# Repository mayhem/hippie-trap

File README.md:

# led-chandelier
LED bottle chandelier built for Nowhere 2015

by Robert Kaye and David Martin

Mock-up
=======

For a render of what we think this might look like a look in the design folder.

Hardware notes
==============

The chandalier made up of about 100 bottles that will have circuit boards with LEDs
inside them. 4 RGD LEDs (WS2812B) connected to an atmega128 will light up each bottle.
Communication happens over a bone simple serial connection, hopefully at 250kbps.
For serial timing and ram reasons, I chose the atmega128 over the attiny84.

The bottles will be connected to 5V power, ground and a communication line. The communication
will be via a line driver that broadcasts the serial signal to each bottle. The RPi can then
send either color information to each bottle or more interestingly send a crude set of instructions
on how to build a color animation. This way the chanelier can work in a centrally coordinated
mode or each bottle carrying out its own program.

.brd and .sch files for Eagle are in hardware folder.

Notes about the circuit
-----------------------

- Regulated 5V power supply in the body of the chandelier
- WS2812B LEDS: http://www.adafruit.com/datasheets/WS2812B.pdf
- MCU: atmega168
- Shottky diodes on the inputs.
- Program via a pogoplug, no actual connector will be on the board.

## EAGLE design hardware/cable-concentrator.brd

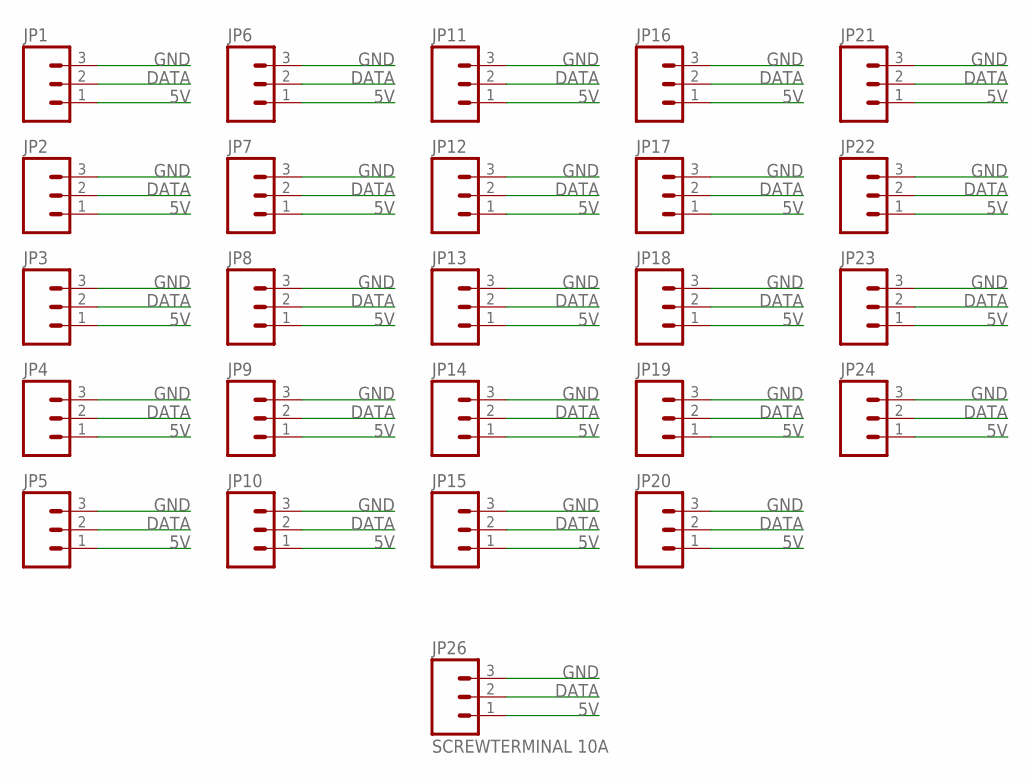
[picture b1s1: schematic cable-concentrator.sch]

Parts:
JP1, JP2, JP3, JP4, JP5, JP6, JP7, JP8, JP9, JP10, JP11, JP12, JP13, JP14, JP15, JP16, JP17, JP18, JP19, JP20, JP21, JP22, JP23, JP24: M03PTH; 1X03
JP26: SCREWTERMINAL 10A; SCREWTERMINAL-3.5MM-3

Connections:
5V: JP1.1, JP2.1, JP3.1, JP4.1, JP5.1, JP6.1, JP7.1, JP8.1, JP9.1, JP10.1, JP11.1, JP12.1, JP13.1, JP14.1, JP15.1, JP16.1, JP17.1, JP18.1, JP19.1, JP20.1, JP21.1, JP22.1, JP23.1, JP24.1, JP26.1
DATA: JP1.2, JP2.2, JP3.2, JP4.2, JP5.2, JP6.2, JP7.2, JP8.2, JP9.2, JP10.2, JP11.2, JP12.2, JP13.2, JP14.2, JP15.2, JP16.2, JP17.2, JP18.2, JP19.2, JP20.2, JP21.2, JP22.2, JP23.2, JP24.2, JP26.2
GND: JP1.3, JP2.3, JP3.3, JP4.3, JP5.3, JP6.3, JP7.3, JP8.3, JP9.3, JP10.3, JP11.3, JP12.3, JP13.3, JP14.3, JP15.3, JP16.3, JP17.3, JP18.3, JP19.3, JP20.3, JP21.3, JP22.3, JP23.3, JP24.3, JP26.3

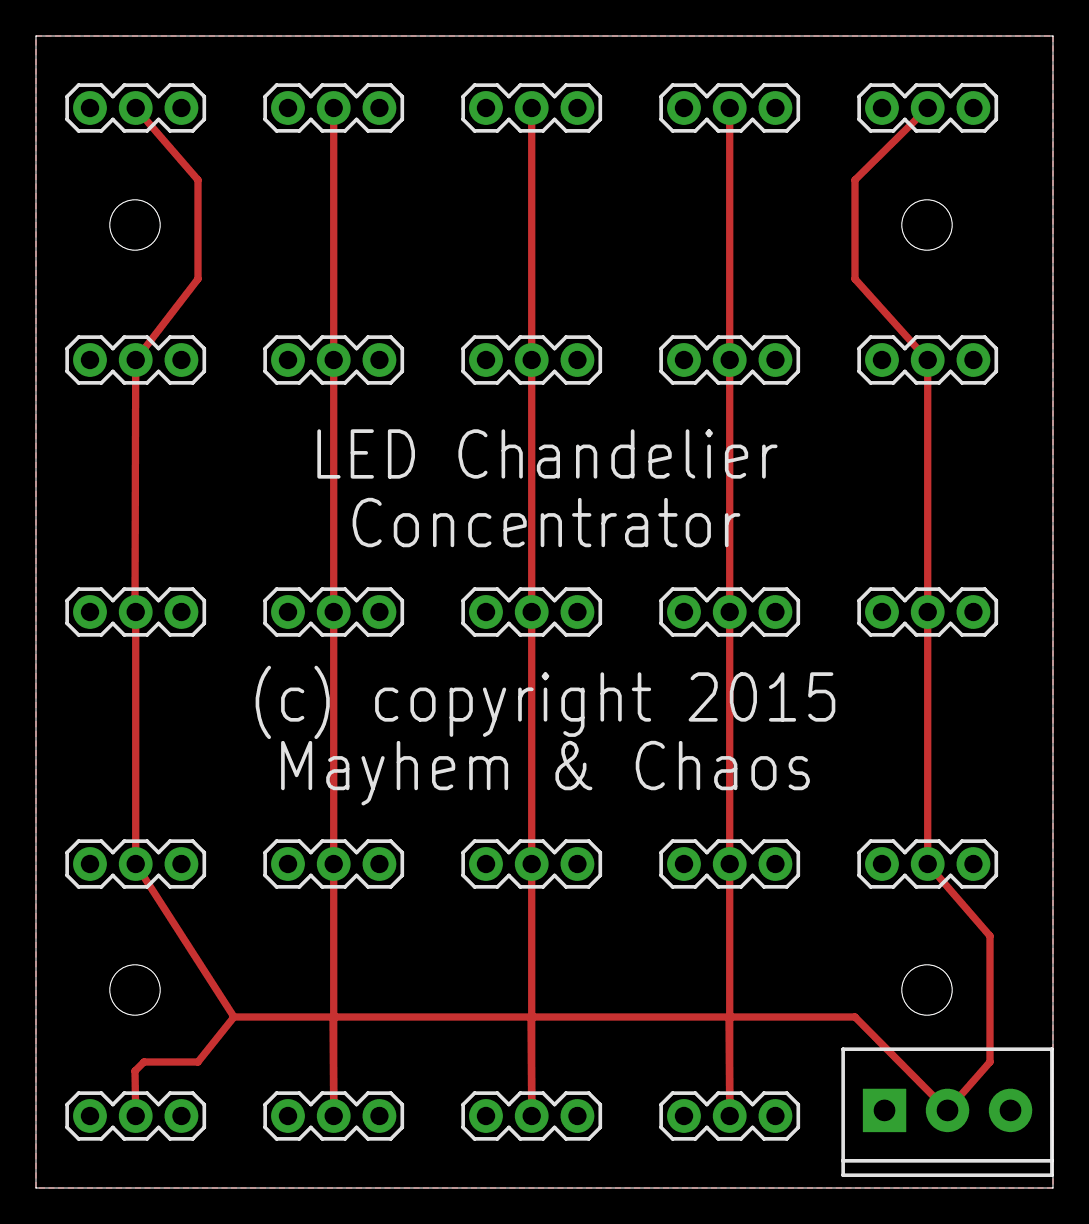
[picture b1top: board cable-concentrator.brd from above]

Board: 2 copper layers, 56.5 x 64.0 mm, 25 parts (0 on the bottom side), 3 nets.

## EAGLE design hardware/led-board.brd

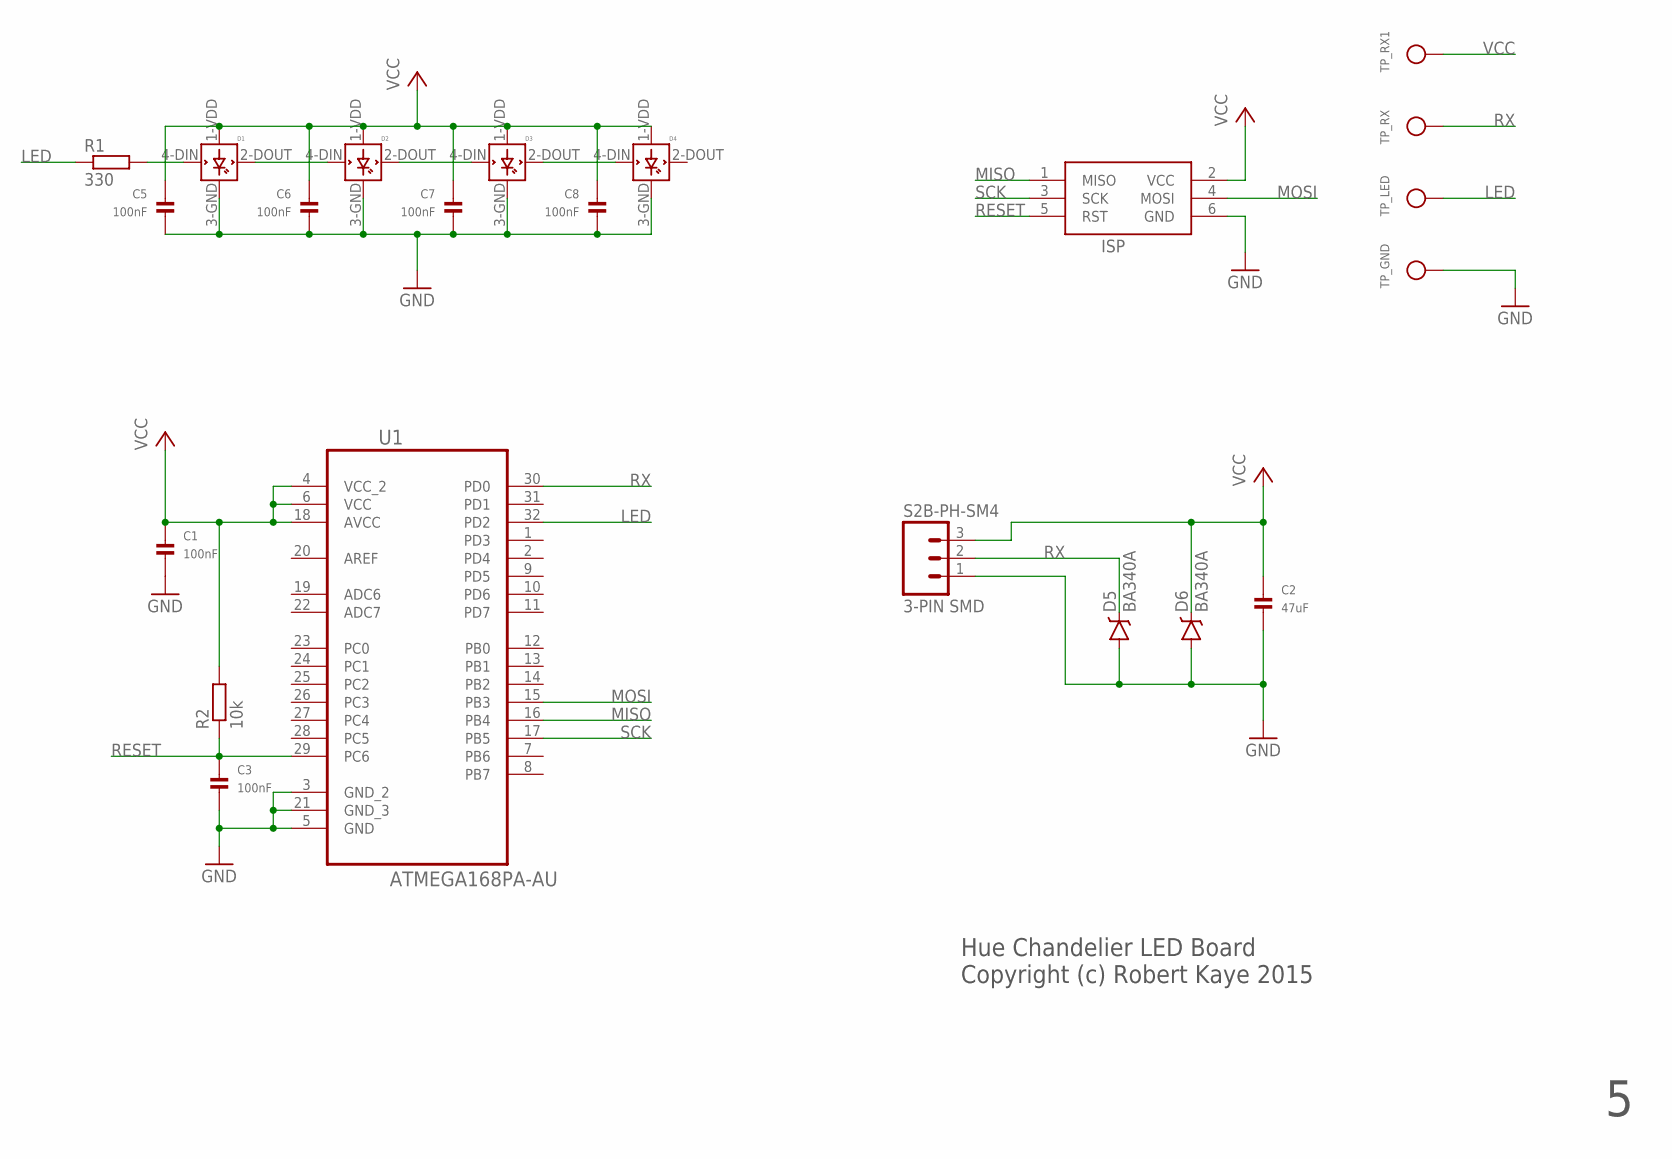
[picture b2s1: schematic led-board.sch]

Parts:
C1, C3, C5, C6, C7, C8: 100nF; 0805; MPN MCSH21B104K250CT
C2: 47uF; 1206; MPN CC0805KKX7R7BB105
D1, D2, D3, D4: WS2812B; MPN WS2812B
D5, D6: BA340A; SMA-DIODE; MPN B330A-13-F
ISP: AVRISP-6; AVRISP
R1: 330; R0805; MPN RC0805JR-07330RL
R2: 10k; R0805; MPN RT0805FRE0710KL
S2B-PH-SM4: 3-PIN SMD; JST-3-SMD; MPN S3B-PH-SM4-TB(LF)(SN)
TP_GND: TESTPOINT1.5X2.0MM_NOCREAM; PAD-1.5X2.0
TP_LED: TESTPOINT1.5X2.0MM_NOCREAM; PAD-1.5X2.0
TP_RX, TP_RX1: TESTPOINT1.5X2.0MM_NOCREAM; PAD-1.5X2.0
U1: ATMEGA168PA-AU; QFP80P900X900X120-32N

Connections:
D3: D2.2-DOUT (DOUT), D3.4-DIN (DIN)
GND: C1.2, C2.2, C3.2, C5.2, C6.2, C7.2, C8.2, D1.3-GND (GND), D2.3-GND (GND), D3.3-GND (GND), D4.3-GND (GND), D5.A, D6.A, ISP.6 (GND), S2B-PH-SM4.1, TP_GND.P$1, U1.3 (GND_2), U1.5 (GND), U1.21 (GND_3)
LED: R1.1, TP_LED.P$1, U1.32 (PD2)
MISO: ISP.1 (MISO), U1.16 (PB4)
MOSI: ISP.4 (MOSI), U1.15 (PB3)
unnamed: D3.2-DOUT (DOUT), D4.4-DIN (DIN)
unnamed: D1.2-DOUT (DOUT), D2.4-DIN (DIN)
unnamed: D1.4-DIN (DIN), R1.2
RESET: C3.1, ISP.5 (RST), R2.1, U1.29 (PC6)
RX: D5.C, S2B-PH-SM4.2, TP_RX.P$1, U1.30 (PD0)
SCK: ISP.3 (SCK), U1.17 (PB5)
VCC: C1.1, C2.1, C5.1, C6.1, C7.1, C8.1, D1.1-VDD (VDD), D2.1-VDD (VDD), D3.1-VDD (VDD), D4.1-VDD (VDD), D6.C, ISP.2 (VCC), R2.2, S2B-PH-SM4.3, TP_RX1.P$1, U1.4 (VCC_2), U1.6 (VCC), U1.18 (AVCC)

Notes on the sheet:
Hue Chandelier LED Board Copyright (c) Robert Kaye 2015

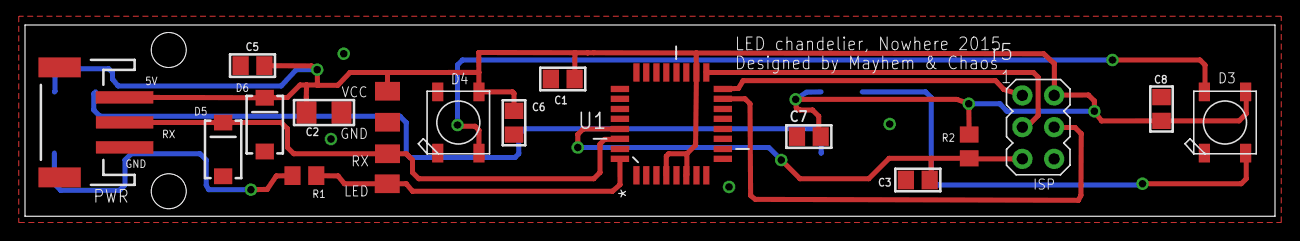
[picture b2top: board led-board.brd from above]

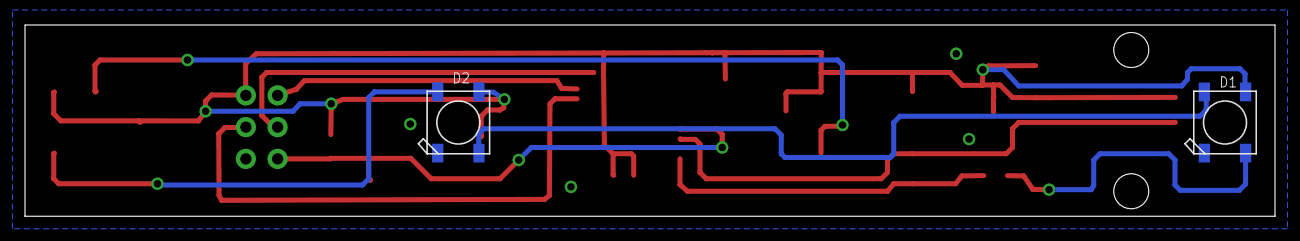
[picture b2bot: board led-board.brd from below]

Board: 2 copper layers, 100.0 x 15.3 mm, 22 parts (2 on the bottom side), 12 nets.

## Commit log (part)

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2015-04-09 Only darkness before this commit
2015-04-09 Added the basic node firmware
2015-04-09 Finished layout and silkscreen work
2015-04-10 test version of a master node
2015-04-10 Brining in the proof of concept RPI code
2015-04-11 Got basic serial comms working
2015-04-11 Basic working node code, updated schematic and layout
2015-04-13 Fixed the orientation of the shottky diodes, improved the layout a bit
2015-04-13 Finished layot and silkscreening. Hopefully ready to go!
2015-04-13 Update README.md
    Adding names.
2015-04-14 Added mounting holes. Might be done now!
2015-04-14 Function generators!
2015-04-14 Increased bulk capacitance (C1) to 47uF.
2015-04-14 Starting with fancy pants music sysnthesis approach to making pretty lights.
2015-04-16 Interim check-in
2015-04-16 Renamed files to be singular
2015-04-16 Added amplitude support and tested sine
2015-04-18 Tools to program node ids
2015-04-18 Added support for ids and packet types and added color array packet type
2015-05-06 Change the yellow to be more orange
2015-05-20 Added code to describe the parameters that need to be sent to the chandelier. Reworked an existing pattern to not use state or an external while loop. I understand functional programming now!! (While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
2015-05-20 Cleanup and simplification.
2015-05-23 Finished implementing and debuggin serializing and reading. Evaluation is next!
2015-05-30 Debugged the generator functions. Verified visually.
2015-05-30 The code works for values |t| < 2000, but it gets inaccurate beyond that. :(
2015-05-31 Implemented sawtooth function
2015-06-01 Interim commit
2015-06-02 Moving things to classes -- interim check-in. Nearly finished with functions.
2015-06-02 Finished implementing the basic functions needed to test the proof of concept. Now I just need to call the functions and generate some output!
2015-06-04 Finished porting source back to C
2015-06-04 Interim check in. Not compiling even. :)
2015-06-06 Seems basic setup works for at least one function.
2015-06-06 Implemented hsb to rgb using integer math
2015-06-06 Finished debugging the rainbow/wobble. Improve generator parameter ordering consistency
2015-06-07 Ported code to aduino and it looks like everything should fit!!!
2015-06-07 2 patterns work correctly!
2015-06-07 2 patterns work, but only one before something gets unhappy.
2015-06-09 Add support for sending random number seeds. Refactor sending of packets
2015-06-09 Remote controlling of patterns now works.
2015-06-09 Finished debugging the ability to load two patterns into ram at once
2015-06-11 Implemented error support with color coding scheme
2015-06-11 Added transition support
2015-06-11 Implemented speed and fixed transitions.
2015-06-11 Some stuff is debugged, but most everything is somewhat broken. :/
2015-06-11 Debugging, but lots of bugs in transitions.
2015-06-12 Started work on addresses
2015-06-13 Refactoring chandelier code a little
2015-06-13 Finished debugging HSV
2015-06-14 The C code now fully behaves in the same way at the python code! \ø/
2015-06-14 Fixed old direct drive mode
2015-06-15 Implemented operators for sources
2015-06-20 Basic text box with styling
2015-06-20 Added submit function, but back-end not implemented yet
2015-06-21 Implemented complementary color source and constant function generator
2015-06-22 another WIP
2015-06-22 partially implemented local functions
2015-06-22 Finished debugging local functions
2015-06-23 Added a plotting function for generators!
2015-06-23 Increase granularity of sin table
2015-06-23 Implemented broadcast classes
2015-06-23 Add reference graphs for the generators
2015-06-23 Implemented a server version of repeat local random number
2015-06-24 Random color sequence is working!
2015-06-24 Don't cast the const value to 8 bit
2015-06-24 Clamp HSV inputs properly, fix a wrong function pointer call
2015-06-24 Allow indefinite debug and command line arg for local not local on dev.py
2015-06-24 Fixed and tested speed setting
2015-06-24 Tested clear next pattern, moved test scripts to tests dir
2015-06-24 Set speed to 100% upon startup
2015-06-25 Implemented the C++ side of timer calibration
2015-06-25 Fix sending entropy to all the nodes
2015-06-26 Added the finished RGB -> HSV function
2015-06-26 Implemented color shift filter
2015-06-26 Added constant random color
2015-06-26 Debugged constant random color
2015-06-26 Debugged color filtering. Still one bug remains in RGB to HSV
2015-06-26 Debugged node id setting and classes
2015-06-26 Debgged complementary colors
2015-06-27 Timing debugged, actual bottles are working fine
2015-06-27 Tuned packet size based on heap/stack inspection
2015-06-27 After tuning max packet size, added a check for exceeding the packet size
2015-06-28 Added RGBSource. Added ability to skip a frame. Properly implemented top level filter.
2015-06-28 Added support for sending position
2015-06-28 implemented a new time calibration routine that works!
2015-06-28 Improved time calibration
2015-06-28 Ditched color filter and implemented simple brightness
2015-06-28 Color shift filter fixes, added fade test
2015-06-28 Change complementary function to use a func as dist
2015-06-28 Change complementary function to use func for dist
2015-06-29 Allow for negative time and fix and made python and c's % consistent
2015-06-29 Changed color to be a src argument for comp color
2015-06-29 Added support for the third source op (for +, -)
2015-06-29 Minor fix on src op
2015-06-29 Finished the XYZ function. Let's hope it works. :)
2015-06-29 First cut at XYZ source. it compiles!
2015-06-29 Debugged the XYZ source.
2015-06-30 Fixed sending positions
2015-06-30 Minor tweaks to programming setup
2015-06-30 Reworked the whole script for progamming nodes
2015-07-01 I hate level shifters. I love atmels. :)
2015-07-01 Implemented live coding!
2015-07-02 Entropy is now 4 bytes and use only three colors at startup
2015-07-04 Committing changes from the desert:
    55ab94309cf93387026938f35b86b5d3a23fd02b 19d6c84e2b0a3d63f62f3f931567741c8993bf1f Robert Kaye <rob@musicbrainz.org> 1435874290 +000 commit: Desert hacking!
    19d6c84e2b0a3d63f62f3f931567741c8993bf1f 57783c7ede4a130361c9ac590669f69f0a9afd72 Robert Kaye <rob@musicbrainz.org> 1435882204 +000 commit: Possibly fix it!
    57783c7ede4a130361c9ac590669f69f0a9afd72 01041ae2d82dbe030008152e4dc76a8f78ba0bd2 Robert Kaye <rob@musicbrainz.org> 1435882509 +000 commit: Fixed the bug!
    Whatever those mean. :)
2015-07-05 Added control end points
2015-07-05 Finished debugging the relay
2015-07-05 Implemented brightness and speed control
2015-08-03 Updated the interface to not use HTTP
2016-01-08 Now the base is even cool!
2016-01-13 Hopefully final versions of the wood cuts for the flower
2016-01-17 Change support for how IDs are assigned
2016-01-17 Added support for local angles
2016-01-17 Finish debugging radial support
2016-01-17 Finished debugging and improving pattern classes.
2016-01-17 Trying to fix GenOp, no luck so far. Will work on that later.
2016-01-19 Fixed reverse pattern for local angle
2016-01-19 It is coming together!
2016-02-03 ORD camp fixes
2017-09-07 Checking nearly complete concentrator
2017-09-10 Start cleanup, and fixup after core function rewrite
2017-09-11 Rewrite complete, square functions work
2017-10-28 Got bootloader hello world working.
2017-10-29 Save before ditching arduino.
2017-10-29 Another interim check in
2017-10-29 It compiles!
2017-10-29 Improve bootloader on and off
2017-10-30 non-arduino codebase seems to be working!
2017-11-01 Interim check in trying to get things sane
2017-11-02 Get a sanity check and off working with the new setup.
2017-11-02 Another interim check-in as the multi-upload features get debugged.
2017-11-02 Calibration improvements
2017-11-02 More bootloader tweaks and debugging
2017-11-03 More tweaks, more debugging. Resets from node work, but still don't enter the bootloader
2017-11-03 Bootloader is getting there, but the node does not reboot into the bootloader.
2017-11-03 Happy with the bootloader so far. I bet I'll find ways it needs improving later.
2017-11-05 add a set_error() function for improved error handling
2017-11-09 Make an error a pattern
2017-11-09 Make the error function a normal pattern
2017-11-10 Messy!
2017-11-10 Found minor problem in packet receiving code. Now CRC checking works correctly.
2018-04-16 Implement more functions, including the critical rainbow function
2018-04-16 Adjustments to bootloader for greater resiliency
2018-04-16 Fix calibrate script
2018-04-17 Started to implement decay, but the code doesn't seem to work. Interim checkin
2018-04-17 Implement setting a single LED
2018-04-17 Minor fixes
2018-04-19 Add panic recovery feature in case bad firmware gets uploaded.
2018-04-19 Adding serial
2018-04-19 Debugging hardening the bootloader
2018-04-20 Program fuses when programming the id
2018-04-22 Finally fixed the fade function
2018-04-22 Increase the panic count
2018-04-23 Add test script for fade pattern
2018-04-23 rename chandelier -> hippietrap
2018-04-23 Port fire and ice to fade
2018-04-23 Simplify more code, remove redundancies, fix fading
2018-04-24 First attempt at a fade out. Not very good, but better than just off
2018-05-09 Refactor to have RPi turn off serial port when not running.
2018-05-12 Fix uploding since new interrupt driven serial io
2018-05-12 use BOD detection
2018-05-12 Toss out the forced bootloader crap for now.
2018-05-12 Use bottle entropy for internal rainbow pattern
2018-05-12 Turn off brightness control it crashed everything again. Now trying forcing to bootloader via the startup sequence
2018-05-13 More debugging for robustness
2018-05-14 Classes have been renamed to groups and seem to work!
2018-05-14 Brightness still doesn't work right. Giving up for now.
2018-05-15 Silly noddling around.
2018-05-26 Add fade to random color support
2018-05-28 Added geometry class to helping with common bottle enumerations. Implemented some sweet sweep patterns
2018-06-10 Software changes for new SSR power control
2018-06-11 The clock is starting to function
2018-06-11 The clock is working
2018-09-08 Clear screen
2018-09-08 Test new sin function
2018-09-09 brightness still not fully fixed. sigh.
2018-09-09 Minor tweak
2018-09-09 Major cleanup and standardization of existing patterns -- next step automating them!
2018-09-09 Grduate some patterns
2018-09-09 Refactor to allow dynamic loading of patterns
2018-09-09 move sin things along, but too stoned to solve this now. :)
2018-09-09 Fix swappies, disable sparkle
2018-09-10 Fixing up patterns that relied on being two rings.
2018-09-11 More robustness bits, removing debug
2018-09-11 Added delays and better error checking to node programmer
2018-09-11 Improving patterns, promising!
2018-09-15 More tweaks trying to make patterns look good with 4 levels.
2018-09-18 Finished debugging the new brightness code. Took forever!
2018-09-19 Fix fade patterns to ms, not ticks for more predictable behaviour
2019-01-24 Minor tweaks to patterns
2019-01-25 Connect the hippie trap to MQTTT
2019-01-25 Finished migrating all the patterns.
2019-01-25 Fixe fire ice circles. A little less circley now, but soo good
2019-01-27 Add a left to right sweep transition
2019-01-27 Add a lateral sweep transition
2019-02-01 Somehow the sin function made the brightness code crash. WTF?
2019-06-26 First cut at py3 version. Loads of bugs!
2019-06-27 Start on MQTT clean up
2019-06-27 Fix firmware sending
2019-06-27 Finish reworking core enable/disable power on/off code for good mqtt support
2019-07-04 Sweep in reverse
2019-07-04 Tweaks on the outward pattern
2021-01-03 Fix pyhon3 uploading and other improvements
2021-01-03 Improve sweeping patterns
2021-01-04 Add new checker sweep pattern. Not fully finished, but a nice start
2022-07-28 Implement brightness up/down
2022-07-28 Add next and repeat pattern functionality
2023-05-10 Add hue shift to set color function
2023-12-26 First stab at night time mdoe
2023-12-26 Check in latest improvements before OS upgrade
2023-12-26 Interim check-in after upgrading OS and a few refactor changes
2023-12-26 Make the scheme a feature of the hippie trap

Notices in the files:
hardware/cable-concentrator.brd:
(c) copyright 2015
parts and their libraries:
SparkFun-Connectors: Licensing: Creative Commons ShareAlike 4.0 International - https://creativecommons.org/licenses/by-sa/4.0
microbuilder: This work is placed in the public domain, and may be freely used for commercial and non-commercial work with the following conditions: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
